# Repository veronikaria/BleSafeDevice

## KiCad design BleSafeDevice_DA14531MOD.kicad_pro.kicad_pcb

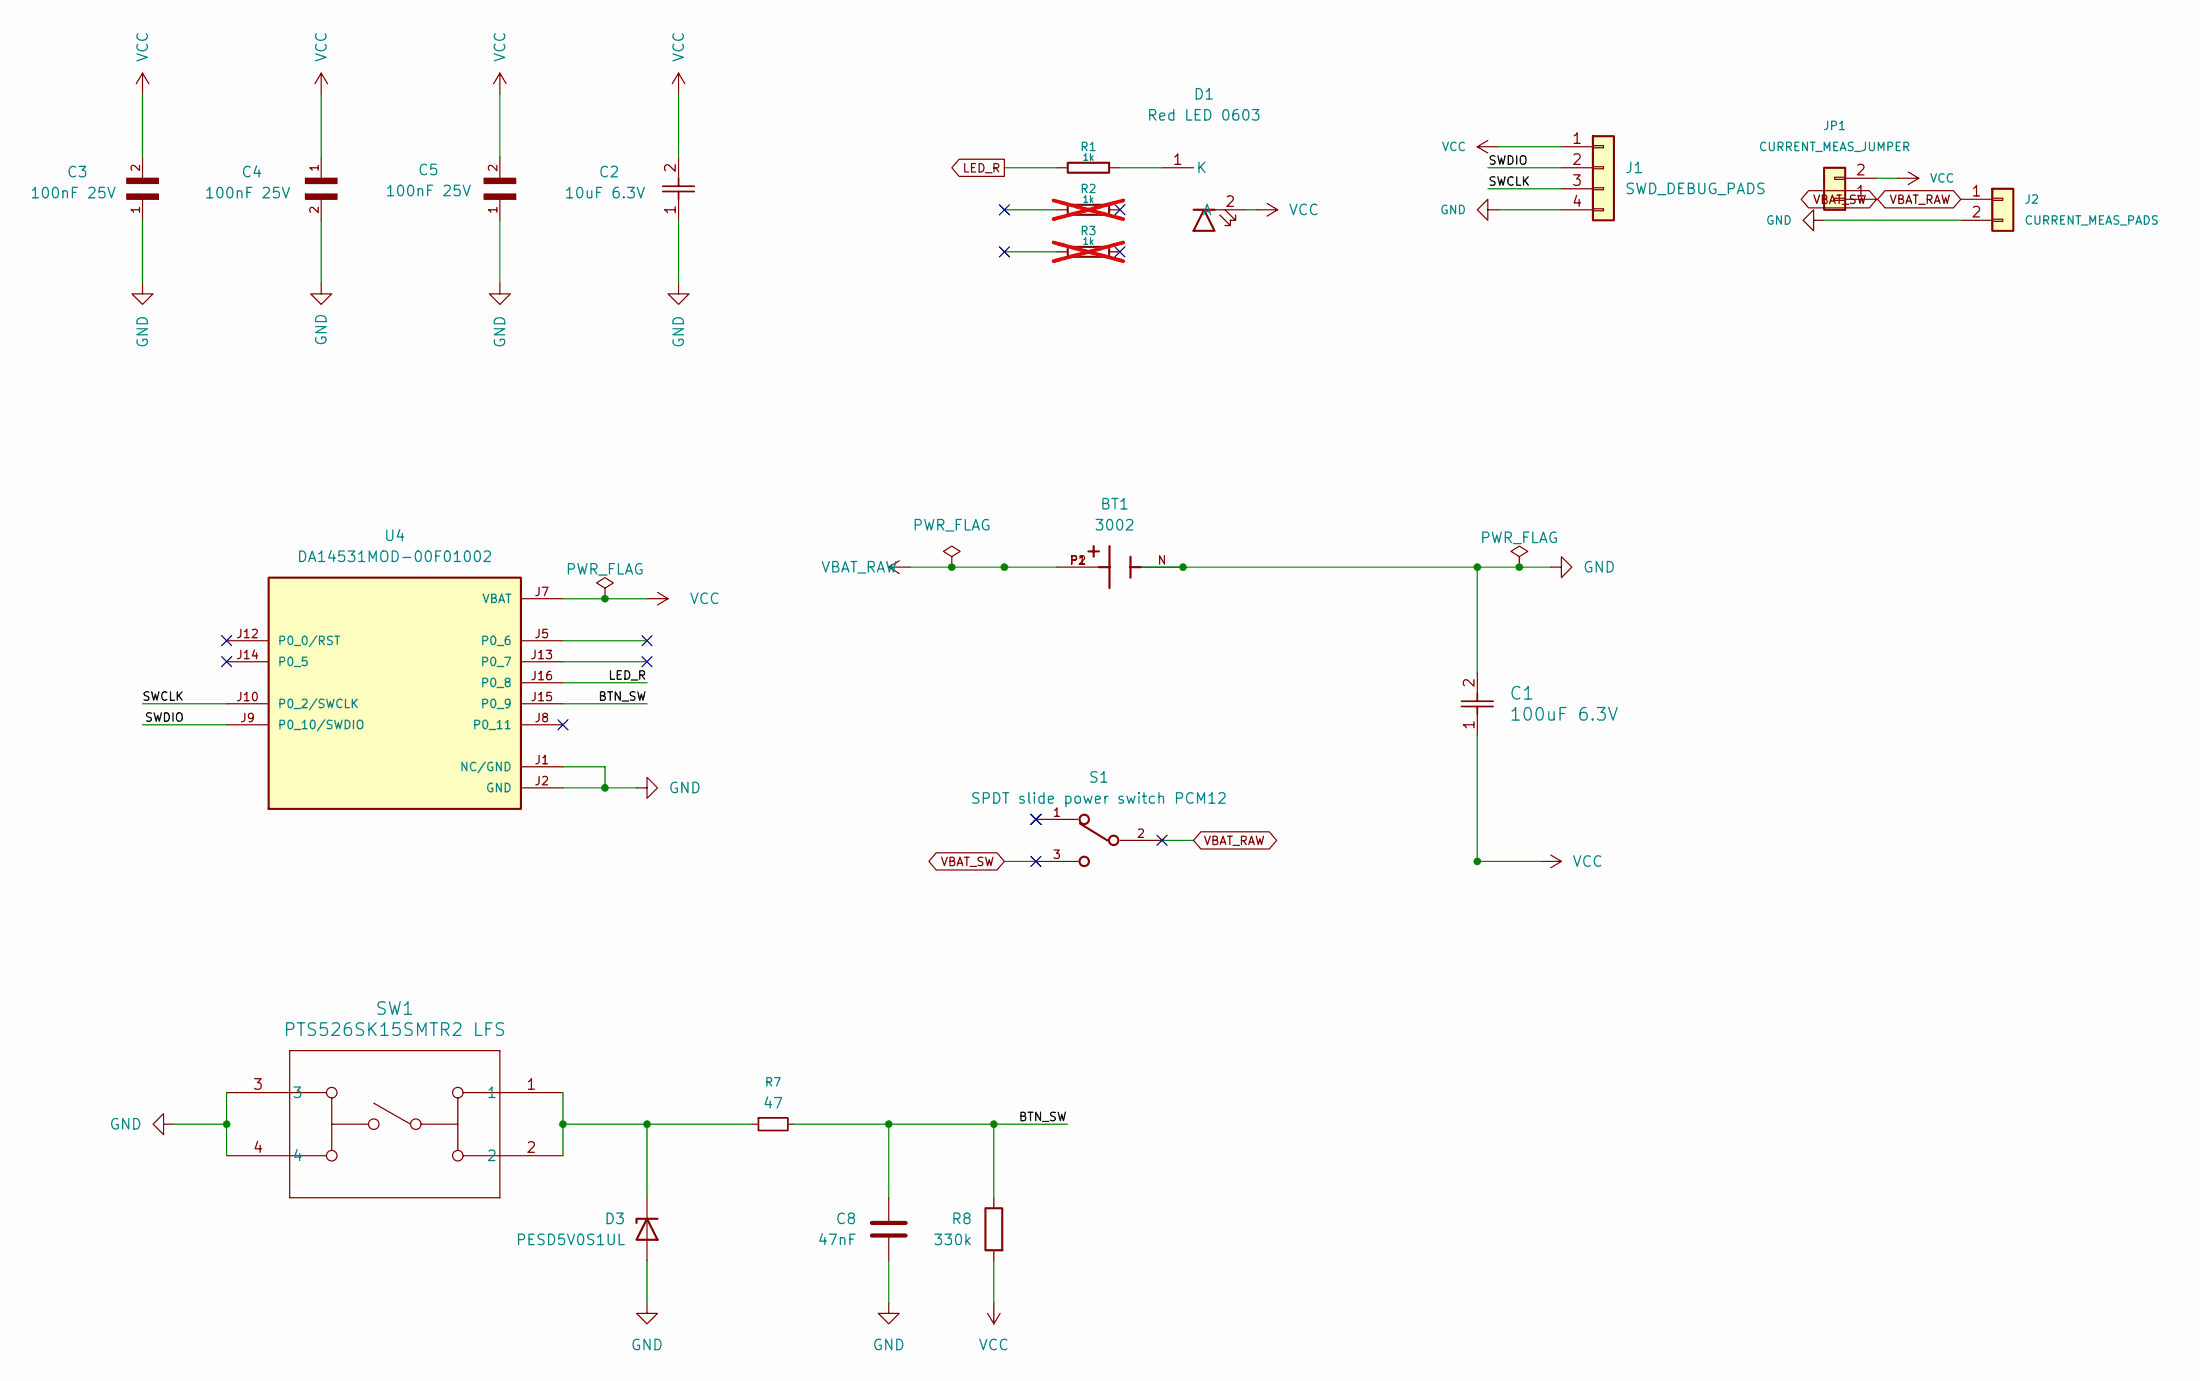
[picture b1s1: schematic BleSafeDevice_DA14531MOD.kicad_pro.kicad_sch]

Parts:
BT1: 3002; BAT_3002; PARTREV T
C1: 100uF 6.3V; C_1210_3225Metric; MPN GRM31CR60J107MEA8K
C2: 10uF 6.3V; C_0805_2012Metric; MPN GRM188R60J106ME47D
C3, C4, C5: 100nF 25V; C_0603_1608Metric
C8: 47nF; C_0603_1608Metric
D1: Red LED 0603; LED_0603_1608Metric_Red_Generic
D3: PESD5V0S1UL; D_SOD-882
J1: SWD_DEBUG_PADS; TP_SWD_1x04_1.27mm_Compact
J2: CURRENT_MEAS_PADS; TP_1x02_1.27mm_Compact
JP1: CURRENT_MEAS_JUMPER; TP_Current_Jumper_2Pad_Compact
R1: 1k; R_0603_1608Metric
R2, R3: 1k; R_0603_1608Metric; not fitted
R7: 47; R_0603_1608Metric
R8: 330k; R_0603_1608Metric
S1: SPDT slide power switch PCM12; SW_SPDT_PCM12
SW1: PTS526SK15SMTR2 LFS; SW_Push_1P1T_NO_CK_PTS526SK15SMTR2_LFS; MPN PTS526SK15SMTR2 LFS
U4: DA14531MOD-00F01002; XCVR_DA14531MOD-00F01002; PARTREV 3.1

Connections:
/BTN_SW: C8.1, R7.2, R8.1, U4.J15 (P0_9)
/SWCLK: J1.3, U4.J10 (P0_2/SWCLK)
/SWDIO: J1.2, U4.J9 (P0_10/SWDIO)
GND: BT1.N, C1.2, C2.1, C3.1, C4.2, C5.1, C8.2, D3.2 (A), J1.4, J2.2, SW1.3, SW1.4, U4.J1 (NC/GND), U4.J2 (GND), U4.J3 (GND), U4.J4 (GND), U4.J6 (GND), U4.J11 (GND)
LED_R: R1.2, U4.J16 (P0_8)
unnamed: D1.1 (K), R1.1
unnamed: D3.1 (K), R7.1, SW1.1, SW1.2
VBAT_RAW: BT1.P1, BT1.P2, J2.1, S1.2
VBAT_SW: JP1.1, S1.3
VCC: C1.1, C2.2, C3.2, C4.1, C5.2, D1.2 (A), J1.1, JP1.2, R8.2, U4.J7 (VBAT)

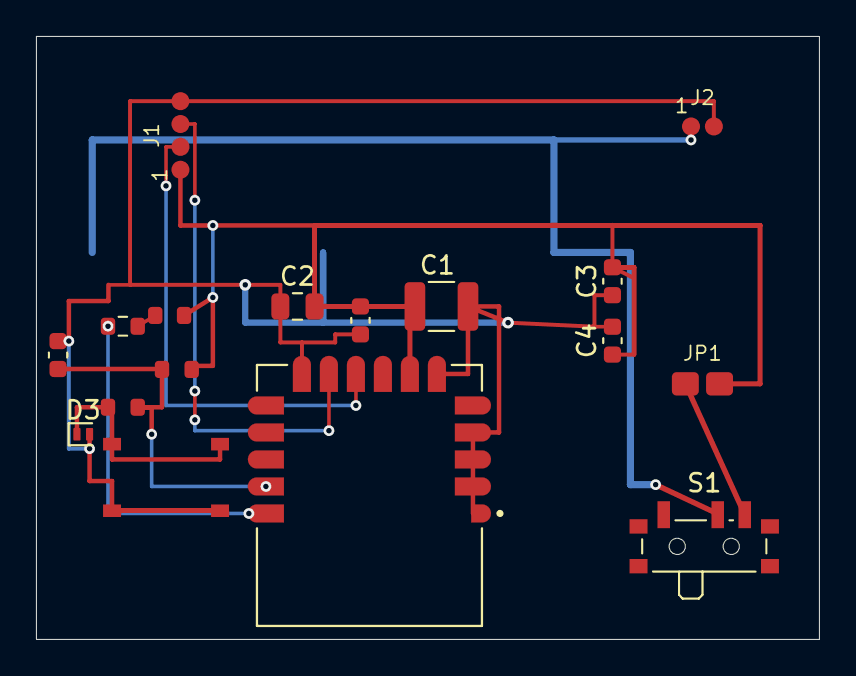
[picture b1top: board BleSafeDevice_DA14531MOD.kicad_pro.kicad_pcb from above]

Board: 2 copper layers, 43.5 x 33.5 mm, 18 parts (1 on the bottom side), 10 nets.

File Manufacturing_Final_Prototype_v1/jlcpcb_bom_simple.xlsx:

Designator | Comment | Footprint | LCSC Part #
BT1 | 3002 | BAT_3002
C1 | 100uF 6.3V | C_1210_3225Metric
C2 | 10uF 6.3V | C_0805_2012Metric
C3 | 0.1uF 25V | C_0603_1608Metric
C4 | 0.1uF 25V | C_0603_1608Metric
C5 | 0.1uF 25V | C_0603_1608Metric
C8 | 47nF | C_0603_1608Metric
D1 | LRTBR48G-P9Q7-1 | LED_RGB_amsOSRAM_LRTBR48G
D3 | PESD5V0S1UL | D_SOD-882
R1 | 1.2K | R_0603_1608Metric
R7 | 47 | R_0603_1608Metric
R8 | 330K | R_0603_1608Metric
SW1 | PTS526SK15SMTR2 LFS | SW_Push_1P1T_NO_CK_PTS526SK15SMTR2_LFS
U4 | DA14531MOD-00F01002 | XCVR_DA14531MOD-00F01002

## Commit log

2026-06-21 Initial KiCad project after footprint library fix
2026-06-21 Add PTS526 low-profile button footprint
2026-06-21 Reconcile button, power switch bypass, and bulk capacitor
2026-06-21 Simplify DA14531 reset and coin-cell power path
2026-06-21 Fix RGB LED footprint and metadata
2026-06-28 Sync PCB with schematic cleanup
2026-06-28 Clean PCB placement after schematic sync
2026-06-28 Replace bulky debug and measurement headers with compact pads
2026-06-28 Route coin-cell power and initial ground paths
2026-06-28 Route DA14531 ground fanout and SWD debug
2026-06-28 Replan PCB placement for button and LED routing
2026-06-28 Restore power and ground routing after layout replan
2026-06-28 Route SWD and button network
2026-06-28 Route button pull-up and partial RGB LED nets
2026-06-28 Simplify LED to red status channel and complete routing
2026-06-28 Clean DRC warnings for prototype candidate
2026-06-28 Generate manufacturing dry run package
2026-06-28 Clear courtyard overlaps for prototype layout
2026-06-28 Fix schematic PCB parity for prototype LED simplification
2026-06-28 Generate final prototype manufacturing package
2026-06-28 Prototype v1 package before JLC part availability fixes
2026-06-28 Replace RGB LED with JLC-friendly red 0603 LED
2026-06-28 Checkpoint before restoring Ping power switch
2026-06-28 Restore production-close Ping power switch
